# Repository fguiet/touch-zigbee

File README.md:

#  Touch-Zigbee

## Forewords

This project aims at creating a ultra low powered capacitive XBee enabled touch button.

It can be used to replace mechanical on/off switch to turn on/off a lamp for instance.

Mecanical swich should be me removed and wire connected so that the lamp is always ON.

Less than 10 uA is required to make this stuff work :)

__My Use case :__

I have got a Hue lamp in my office. 

Hue lamp can be switch off and on thank to the Philips Hue API.

So I am gonna replace the mecanical on/off swith by the Touch-Zigbee switch.

Here is the workflow:

Touch-Zigbee capacitive switch sends a message to a zigbee reveiver plugged in a Rapsberry.

A nodered flow will listen to the ZigBee messages and call the Philips Hue API to turn the Hue lamp on and off.

Obviously, the API or Nodered communicates with Home Assitant so I can see the Philips Hue Lamp status.

Moreover, I can programm some scenes when not at home to simulate that somebody is at home.

## Documentation

Here is some notes I took when I realized this project : [Project Notes](documentation/touch-zigbee.md)

## Illustrations

* Bare PCB received from JLCPCB and realized with KiCAD 5.1.12

Diameter : only 5 cm (can be insert in a standard French mecanical on/off switch case)

* Assembled PCB 

* Testing XBee communication with XCTU

NB : Version 2.0.0 of this project use XBee API Mode 2 (as you can see of the picture below I was using transparent mode before (AT))

Battery voltage can be read and send :) Nice

A led is blinking when the capacitive sensor is touched :)

* Wall plug design in FreeCAD

* 3D Printing wallplug (not the last version)

* Assembling the whole stuff (I do not have the XBee pin header at you can see, it is coming from China)

* Everything in place (last version remove the little gaps)

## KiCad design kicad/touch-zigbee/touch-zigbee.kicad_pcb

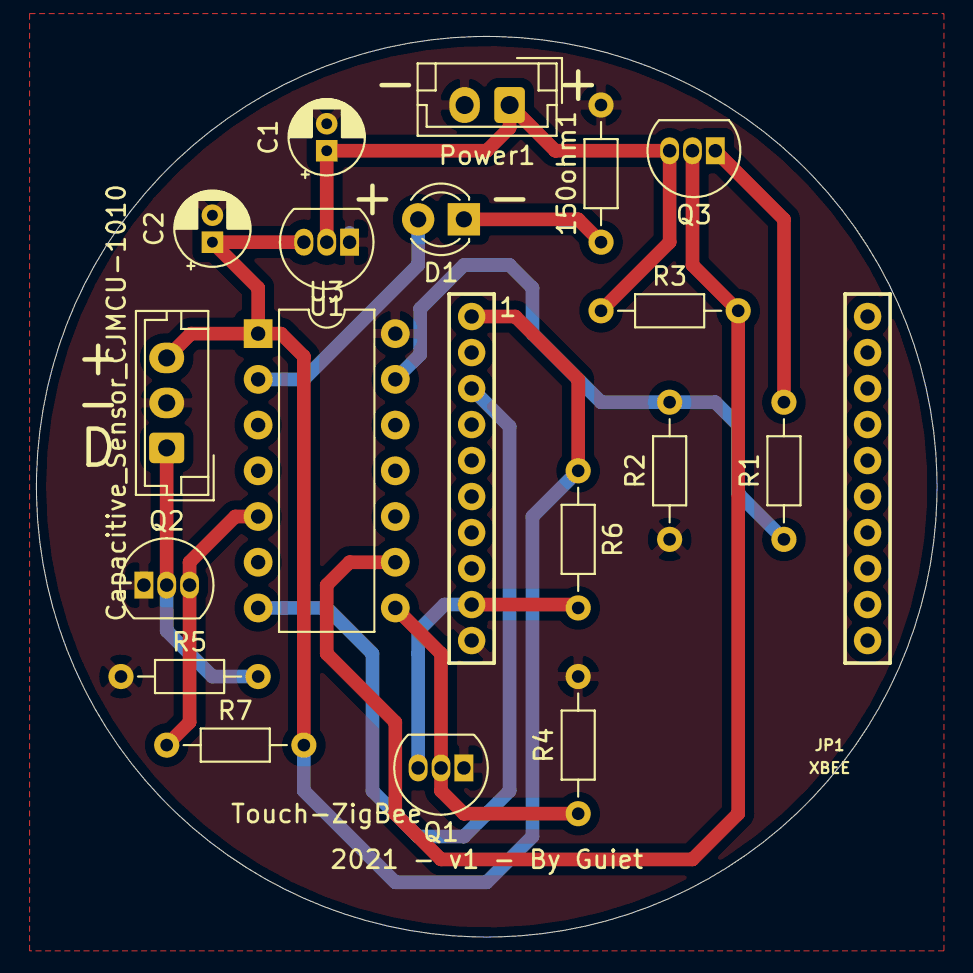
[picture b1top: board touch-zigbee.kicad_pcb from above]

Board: 2 copper layers, 50.0 x 50.0 mm, 19 parts (0 on the bottom side), 13 nets.

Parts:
150ohm1: R; R_Axial_DIN0204_L3.6mm_D1.6mm_P7.62mm_Horizontal
C1, C2: 10uF; CP_Radial_D4.0mm_P1.50mm
Capacitive_Sensor_CJMCU-1010: Conn_01x03_Female; JST_EH_B3B-EH-A_1x03_P2.50mm_Vertical
D1: LED; LED_D3.0mm_IRBlack
JP1: XBEE
Power1: Conn_01x02_Female; JST_EH_B2B-EH-A_1x02_P2.50mm_Vertical
Q1, Q2: 2N7000; TO-92_Inline
Q3: TP0610L; TO-92L_Inline
R1, R3, R4, R5, R6, R7: 10kOhm; R_Axial_DIN0204_L3.6mm_D1.6mm_P7.62mm_Horizontal
R2: 3.3kOhm; R_Axial_DIN0204_L3.6mm_D1.6mm_P7.62mm_Horizontal
U1: 7333-A-TO92; TO-92_Inline
U3: ATtiny84A-PU; DIP-14_W7.62mm

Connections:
+3.3v: C2.1, Capacitive_Sensor_CJMCU-1010.3, JP1.1, R6.1, R7.2, U1.3, U3.1
GND: 150ohm1.2, C1.2, C2.2, Capacitive_Sensor_CJMCU-1010.2, JP1.10, Power1.2, Q1.1, Q2.1, R2.1, R4.2, R5.1, U1.1, U3.14
unnamed: 150ohm1.1, D1.1
unnamed: Capacitive_Sensor_CJMCU-1010.1, Q2.2, R5.2
unnamed: D1.2, U3.2
unnamed: JP1.3, U3.7
unnamed: JP1.9, Q1.3, R6.2
unnamed: Q1.2, R4.1, U3.8
unnamed: Q2.3, R7.1, U3.5
unnamed: Q3.1, R1.2
unnamed: Q3.2, R3.2, U3.9
unnamed: R1.1, R2.2, U3.13
VBAT: C1.1, Power1.1, Q3.3, R3.1, U1.2

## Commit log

2021-12-18 Add freecad plug wall design and add some illustrations
2021-12-19 Minor modification to freecad and program code
2022-01-01 add reference
2024-01-21 Move to Xbee API Mode 2, update doc, update kicad schematic
2024-01-21 update kicad schematic
